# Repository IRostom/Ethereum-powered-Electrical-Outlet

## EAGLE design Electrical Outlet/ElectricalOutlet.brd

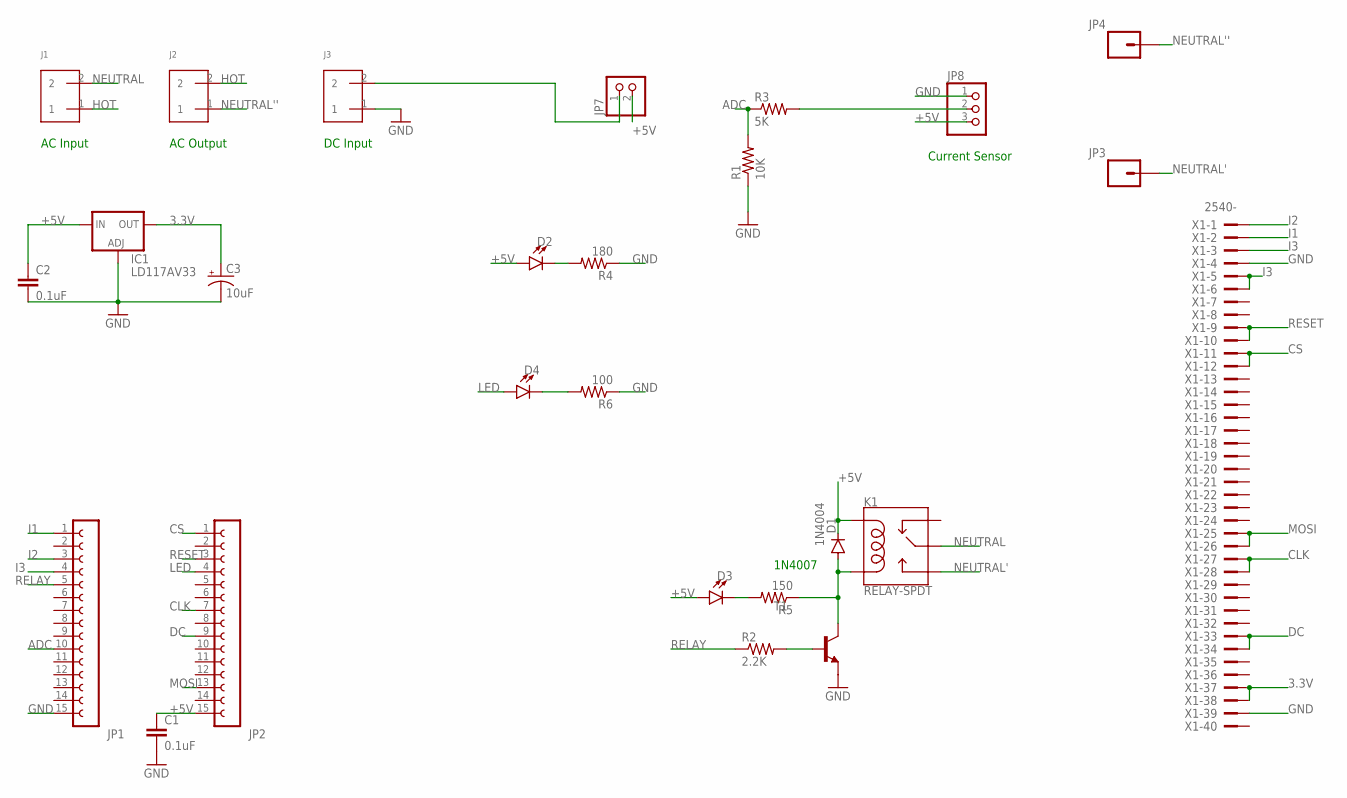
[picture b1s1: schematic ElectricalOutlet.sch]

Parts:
C1, C2: 0.1uF; CAP-PTH-SMALL-KIT
C3: 10uF; CPOL-RADIAL-2.5MM-5MM-KIT
D1: 1N4004; DO41-10
D2, D3, D4: LED3MM; LED_3MM
IC1: LD117AV33; TO220L1
J1, J2, J3: SCREW_TERMINAL; PHEONIX-1935161
JP1, JP2: FE15-1; FE15
JP3, JP4: CONN_01; 1X01
JP7: PINHD-1X2; 1X02
JP8: PINHD-1X3; 1X03
K1: RELAY-SPDT; RELAY_G5LE
R1: 10K; 0204/7
R2: 2.2K; 0204/7
R3: 5K; 0204/7
R4: 180; 0204/7
R5: 150; 0204/7
R6: 100; 0204/7
T1: -NPN-TO92; TO92
X1: 2540-; PAK100/2500-40

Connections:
3.3V: C3.1 (+), IC1.2 (OUT), X1.37, X1.38
+5V: C1.1, C2.1, D1.C, D2.A, D3.A, IC1.3 (IN), JP2.15, JP7.2, JP8.3, K1.2 (COIL1)
ADC: JP1.10, R1.2, R3.1
CLK: JP2.7, X1.27, X1.28
CS: JP2.1, X1.11, X1.12
DC: JP2.9, X1.33, X1.34
GND: C1.2, C2.2, C3.2 (-), IC1.1 (ADJ), J3.1, JP1.15, JP8.1, R1.1, R4.1, R6.1, T1.1 (E), X1.4, X1.39
HOT: J1.1, J2.2
I1: JP1.1, X1.2
I2: JP1.3, X1.1
I3: JP1.4, X1.3, X1.5, X1.6
LED: D4.A, JP2.4
MOSI: JP2.13, X1.25, X1.26
unnamed: D4.K (C), R6.2
unnamed: R2.2, T1.2 (B)
unnamed: D3.K (C), R5.2
unnamed: J3.2, JP7.1
unnamed: D2.K (C), R4.2
unnamed: JP8.2, R3.2
unnamed: D1.A, K1.5 (COIL2), R5.1, T1.3 (C)
NEUTRAL: J1.2, K1.1 (MAIN)
NEUTRAL': JP3.1, K1.3 (NO)
NEUTRAL'': J2.1, JP4.1
RELAY: JP1.5, R2.1
RESET: JP2.3, X1.9, X1.10

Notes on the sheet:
AC Input
AC Output
Current Sensor
1N4007
DC Input

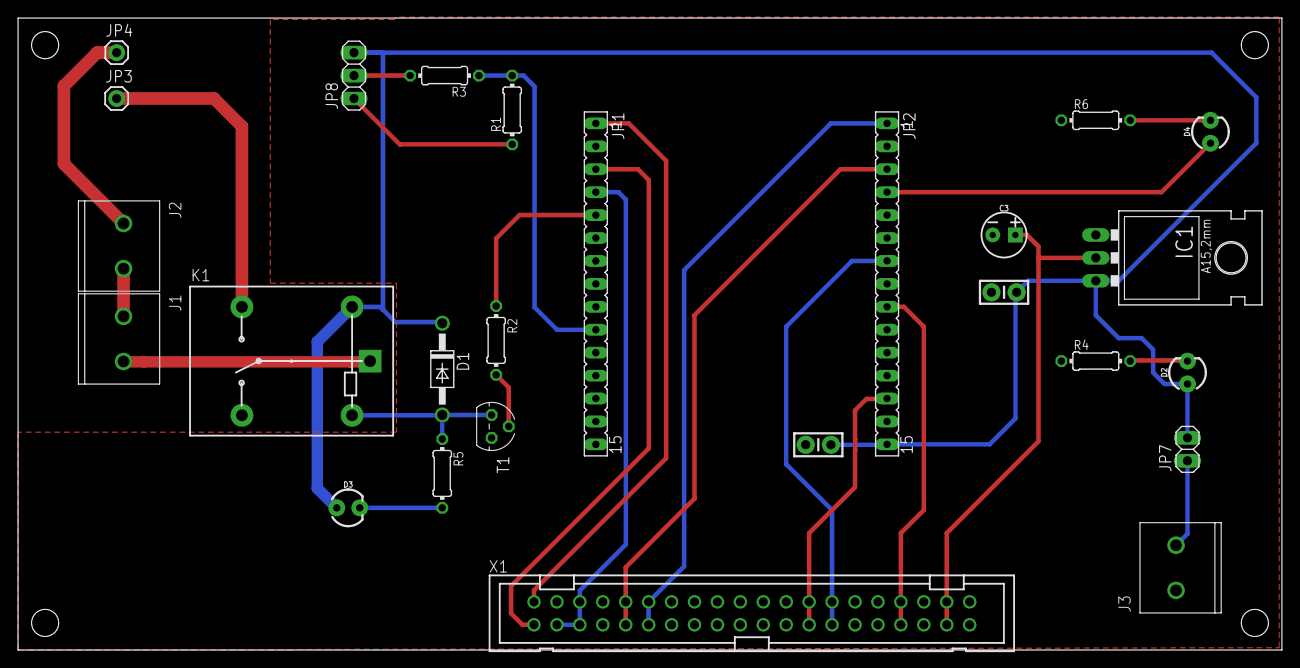
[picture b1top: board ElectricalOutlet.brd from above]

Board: 2 copper layers, 140.0 x 70.0 mm, 26 parts (0 on the bottom side), 25 nets.

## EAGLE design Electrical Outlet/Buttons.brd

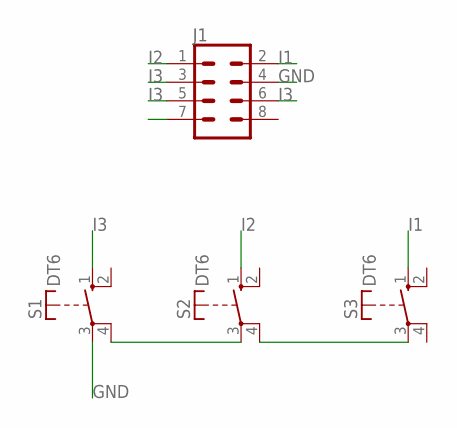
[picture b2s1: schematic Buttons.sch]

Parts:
J1: CONN_04X2; 2X4
S1, S2, S3: DT6

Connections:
GND: J1.4, S1.3
I1: J1.2, S3.1 (S)
I2: J1.1, S2.1 (S)
I3: J1.3, J1.5, J1.6, S1.1 (S)
unnamed: S2.4, S3.3
unnamed: S1.4, S2.3

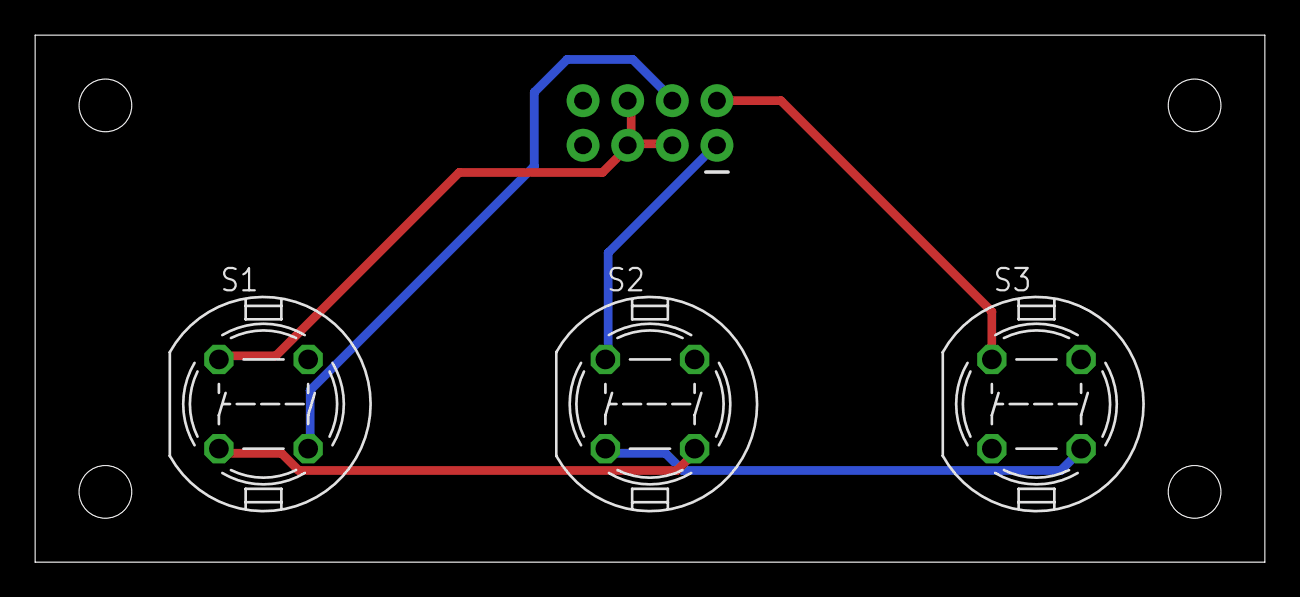
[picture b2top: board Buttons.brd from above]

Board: 2 copper layers, 70.0 x 30.0 mm, 4 parts (1 on the bottom side), 6 nets.

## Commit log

2019-03-24 first and last commit

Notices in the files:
parts and their libraries:
SparkFun-Connectors: Licensing: Creative Commons ShareAlike 4.0 International - https://creativecommons.org/licenses/by-sa/4.0
